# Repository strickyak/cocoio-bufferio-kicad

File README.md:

# cocoio-bufferio-kicad
for diagnostic use

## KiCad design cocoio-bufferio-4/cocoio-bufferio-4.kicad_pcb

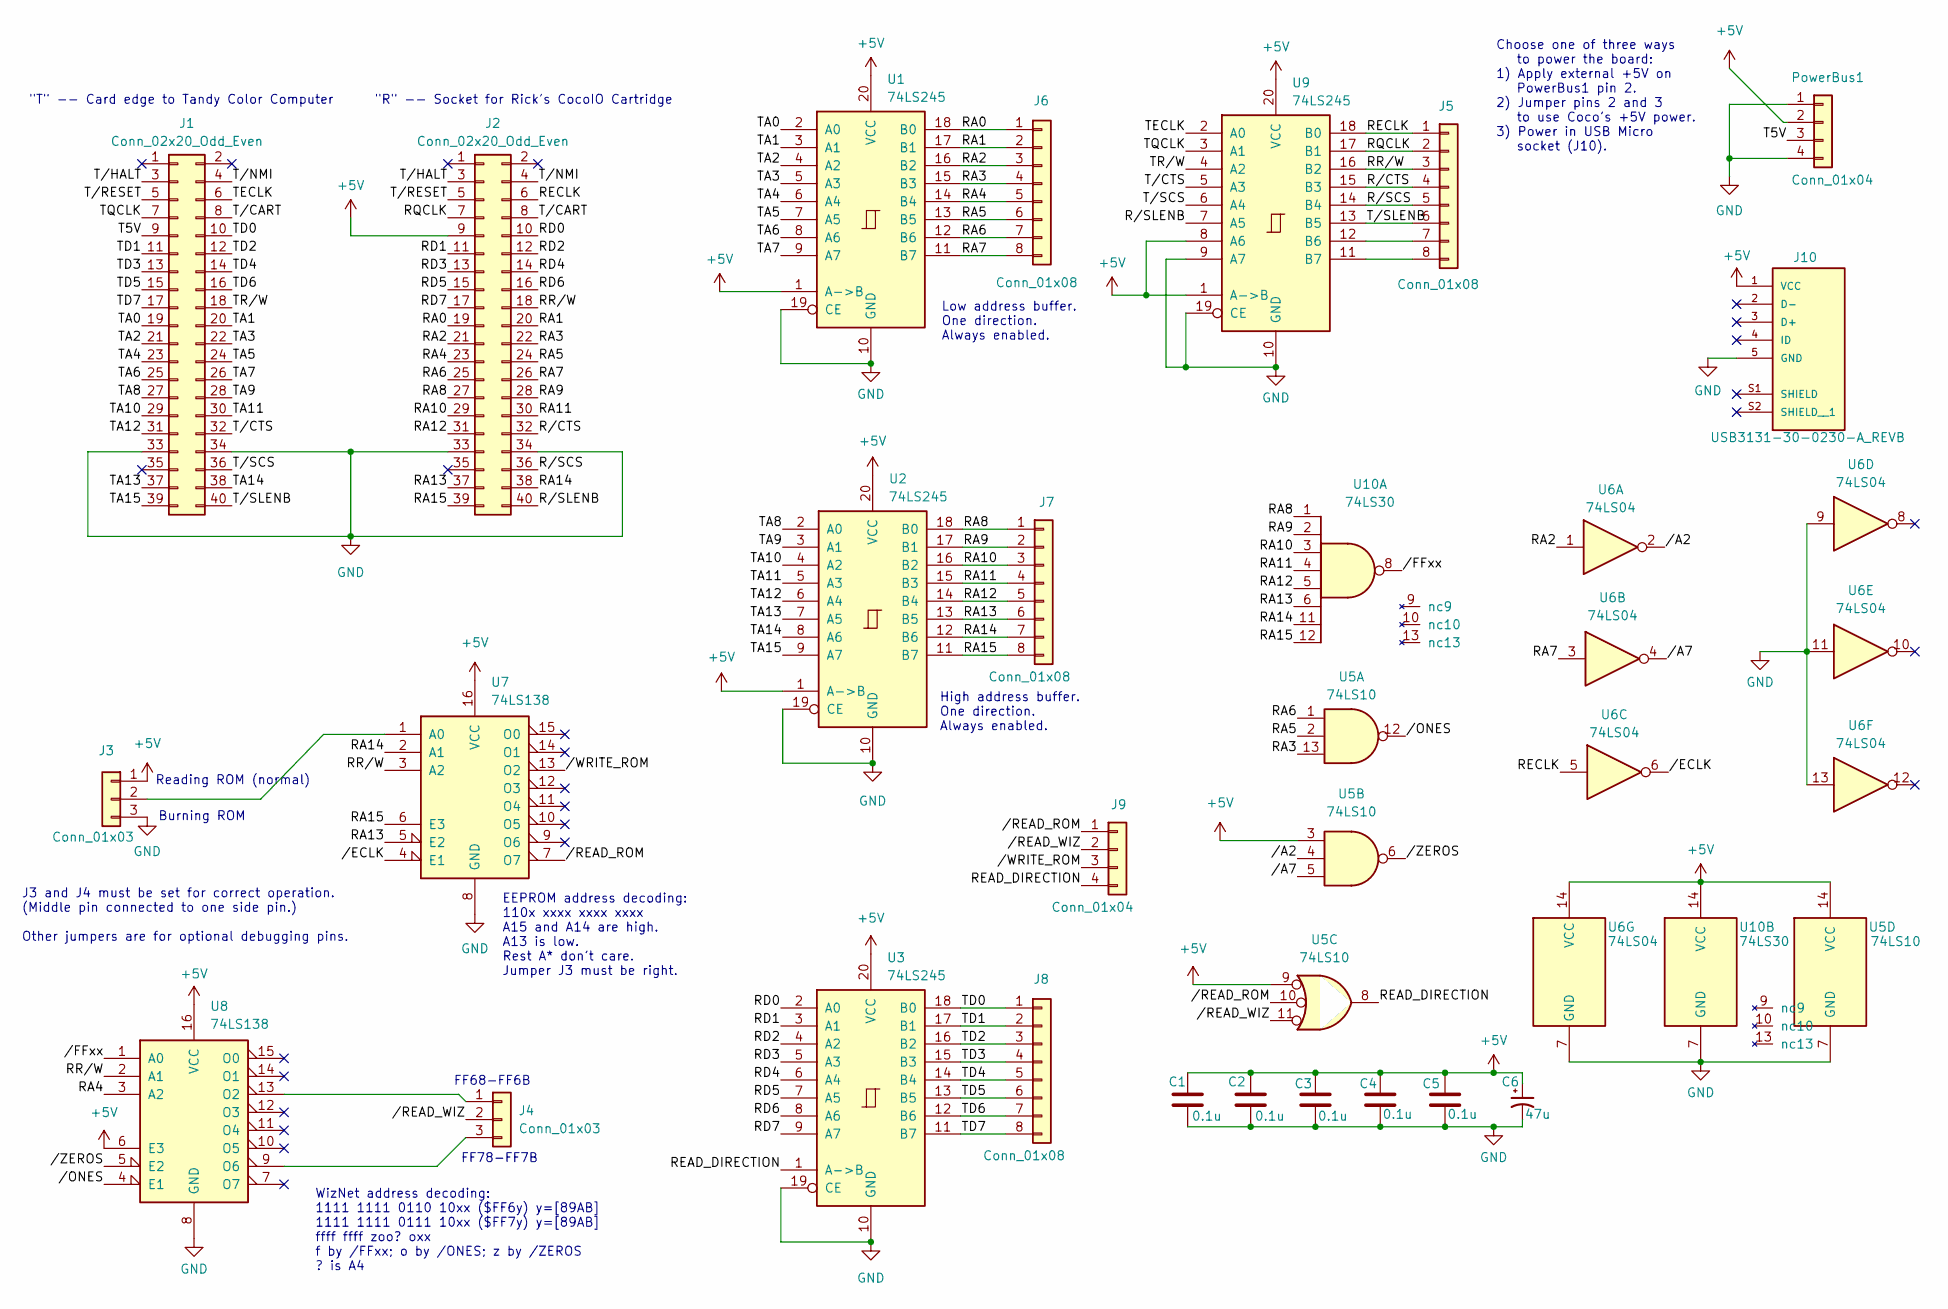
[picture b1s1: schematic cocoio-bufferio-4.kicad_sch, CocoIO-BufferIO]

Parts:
C1, C2, C3, C4, C5: 0.1u; C_Disc_D5.0mm_W2.5mm_P5.00mm
C6: 47u; CP_Radial_D7.5mm_P2.50mm
J1: Conn_02x20_Odd_Even; CocoCardEdge
J2: Conn_02x20_Odd_Even; Coco_Card_Female
J3, J4: Conn_01x03; PinHeader_1x03_P2.54mm_Vertical
J5, J6, J7, J8: Conn_01x08; PinHeader_1x08_P2.54mm_Vertical
J9: Conn_01x04; PinHeader_1x04_P2.54mm_Vertical
J10: USB3131-30-0230-A_REVB; GCT_USB3131-30-0230-A_REVB; PARTREV B4
PowerBus1: Conn_01x04; PinHeader_1x04_P2.54mm_Vertical
U1, U2, U3, U9: 74LS245; DIP-20_W7.62mm_LongPads
U5: 74LS10; DIP-14_W7.62mm_LongPads
U6: 74LS04; DIP-14_W7.62mm_LongPads
U7, U8: 74LS138; DIP-16_W7.62mm_LongPads
U10: 74LS30; DIP-14_W7.62mm_LongPads

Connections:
+5V: C1.1, C2.1, C3.1, C4.1, C5.1, C6.1, J2.9, J3.1, J10.1 (VCC), PowerBus1.2, U1.1 (A->B), U1.20 (VCC), U2.1 (A->B), U2.20 (VCC), U3.20 (VCC), U5.3, U5.9, U5.14 (VCC), U6.14 (VCC), U7.16 (VCC), U8.6 (E3), U8.16 (VCC), U9.1 (A->B), U9.8 (A6), U9.20 (VCC), U10.14 (VCC)
/RA0: J2.19, J6.1, U1.18 (B0)
/RA1: J2.20, J6.2, U1.17 (B1)
/RA2: J2.21, J6.3, U1.16 (B2), U6.1
/RA3: J2.22, J6.4, U1.15 (B3), U5.13
/RA4: J2.23, J6.5, U1.14 (B4), U8.3 (A2)
/RA5: J2.24, J6.6, U1.13 (B5), U5.2
/RA6: J2.25, J6.7, U1.12 (B6), U5.1
/RA7: J2.26, J6.8, U1.11 (B7), U6.3
/RA8: J2.27, J7.1, U2.18 (B0), U10.1
/RA9: J2.28, J7.2, U2.17 (B1), U10.2
/RA10: J2.29, J7.3, U2.16 (B2), U10.3
/RA11: J2.30, J7.4, U2.15 (B3), U10.4
/RA12: J2.31, J7.5, U2.14 (B4), U10.5
/RA13: J2.37, J7.6, U2.13 (B5), U7.5 (E2), U10.6
/RA14: J2.38, J7.7, U2.12 (B6), U7.2 (A1), U10.11
/RA15: J2.39, J7.8, U2.11 (B7), U7.6 (E3), U10.12
/RD0: J2.10, U3.2 (A0)
/RD1: J2.11, U3.3 (A1)
/RD2: J2.12, U3.4 (A2)
/RD3: J2.13, U3.5 (A3)
/RD4: J2.14, U3.6 (A4)
/RD5: J2.15, U3.7 (A5)
/RD6: J2.16, U3.8 (A6)
/RD7: J2.17, U3.9 (A7)
/READ_DIRECTION: J9.4, U3.1 (A->B), U5.8
/RECLK: J2.6, J5.1, U6.5, U9.18 (B0)
/RQCLK: J2.7, J5.2, U9.17 (B1)
/RR/W: J2.18, J5.3, U7.3 (A2), U8.2 (A1), U9.16 (B2)
/R/CTS: J2.32, J5.4, U9.15 (B3)
/R/SCS: J2.36, J5.5, U9.14 (B4)
/R/SLENB: J2.40, U9.7 (A5)
/T5V: J1.9, PowerBus1.3
/TA0: J1.19, U1.2 (A0)
/TA1: J1.20, U1.3 (A1)
/TA2: J1.21, U1.4 (A2)
/TA3: J1.22, U1.5 (A3)
/TA4: J1.23, U1.6 (A4)
/TA5: J1.24, U1.7 (A5)
/TA6: J1.25, U1.8 (A6)
/TA7: J1.26, U1.9 (A7)
/TA8: J1.27, U2.2 (A0)
/TA9: J1.28, U2.3 (A1)
/TA10: J1.29, U2.4 (A2)
/TA11: J1.30, U2.5 (A3)
/TA12: J1.31, U2.6 (A4)
/TA13: J1.37, U2.7 (A5)
/TA14: J1.38, U2.8 (A6)
/TA15: J1.39, U2.9 (A7)
/TD0: J1.10, J8.1, U3.18 (B0)
/TD1: J1.11, J8.2, U3.17 (B1)
/TD2: J1.12, J8.3, U3.16 (B2)
/TD3: J1.13, J8.4, U3.15 (B3)
/TD4: J1.14, J8.5, U3.14 (B4)
/TD5: J1.15, J8.6, U3.13 (B5)
/TD6: J1.16, J8.7, U3.12 (B6)
/TD7: J1.17, J8.8, U3.11 (B7)
/TECLK: J1.6, U9.2 (A0)
/TQCLK: J1.7, U9.3 (A1)
/TR/W: J1.18, U9.4 (A2)
/T/CART: J1.8, J2.8
/T/CTS: J1.32, U9.5 (A3)
/T/HALT: J1.3, J2.3
/T/NMI: J1.4, J2.4
/T/RESET: J1.5, J2.5
/T/SCS: J1.36, U9.6 (A4)
/T/SLENB: J1.40, J5.6, U9.13 (B5)
//A2: U5.4, U6.2
//A7: U5.5, U6.4
//ECLK: U6.6, U7.4 (E1)
//FFxx: U8.1 (A0), U10.8
//ONES: U5.12, U8.4 (E1)
//READ_ROM: J9.1, U5.10, U7.7 (O7)
//READ_WIZ: J4.2, J9.2, U5.11
//WRITE_ROM: J9.3, U7.13 (O2)
//ZEROS: U5.6, U8.5 (E2)
GND: C1.2, C2.2, C3.2, C4.2, C5.2, C6.2, J1.33, J1.34, J2.33, J2.34, J3.3, J10.5 (GND), PowerBus1.1, PowerBus1.4, U1.10 (GND), U1.19 (CE), U2.10 (GND), U2.19 (CE), U3.10 (GND), U3.19 (CE), U5.7 (GND), U6.7 (GND), U6.9, U6.11, U6.13, U7.8 (GND), U8.8 (GND), U9.9 (A7), U9.10 (GND), U9.19 (CE), U10.7 (GND); also elsewhere on the board
unnamed: J3.2, U7.1 (A0)
unnamed: J4.1, U8.13 (O2)
unnamed: J4.3, U8.9 (O6)
unnamed: J5.7, U9.12 (B6)
unnamed: J5.8, U9.11 (B7)

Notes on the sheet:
Burning ROM
WizNet address decoding: 1111 1111 0110 10xx ($FF6y) y=[89AB] 1111 1111 0111 10xx ($FF7y) y=[89AB] ffff ffff zoo? oxx f by /FFxx; o by /ONES; z by /ZEROS ? is A4
J3 and J4 must be set for correct operation. (Middle pin connected to one side pin.) Other jumpers are for optional debugging pins.
FF68-FF6B
Choose one of three ways to power the board: 1) Apply external +5V on PowerBus1 pin 2. 2) Jumper pins 2 and 3 to use Coco's +5V power. 3) Power in USB Micro socket (J10).
"R" -- Socket for Rick's CocoIO Cartridge
EEPROM address decoding: 110x xxxx xxxx xxxx A15 and A14 are high. A13 is low. Rest A* don't care. Jumper J3 must be right.
Reading ROM (normal)
FF78-FF7B
Low address buffer. One direction. Always enabled.
"T" -- Card edge to Tandy Color Computer
High address buffer. One direction. Always enabled.

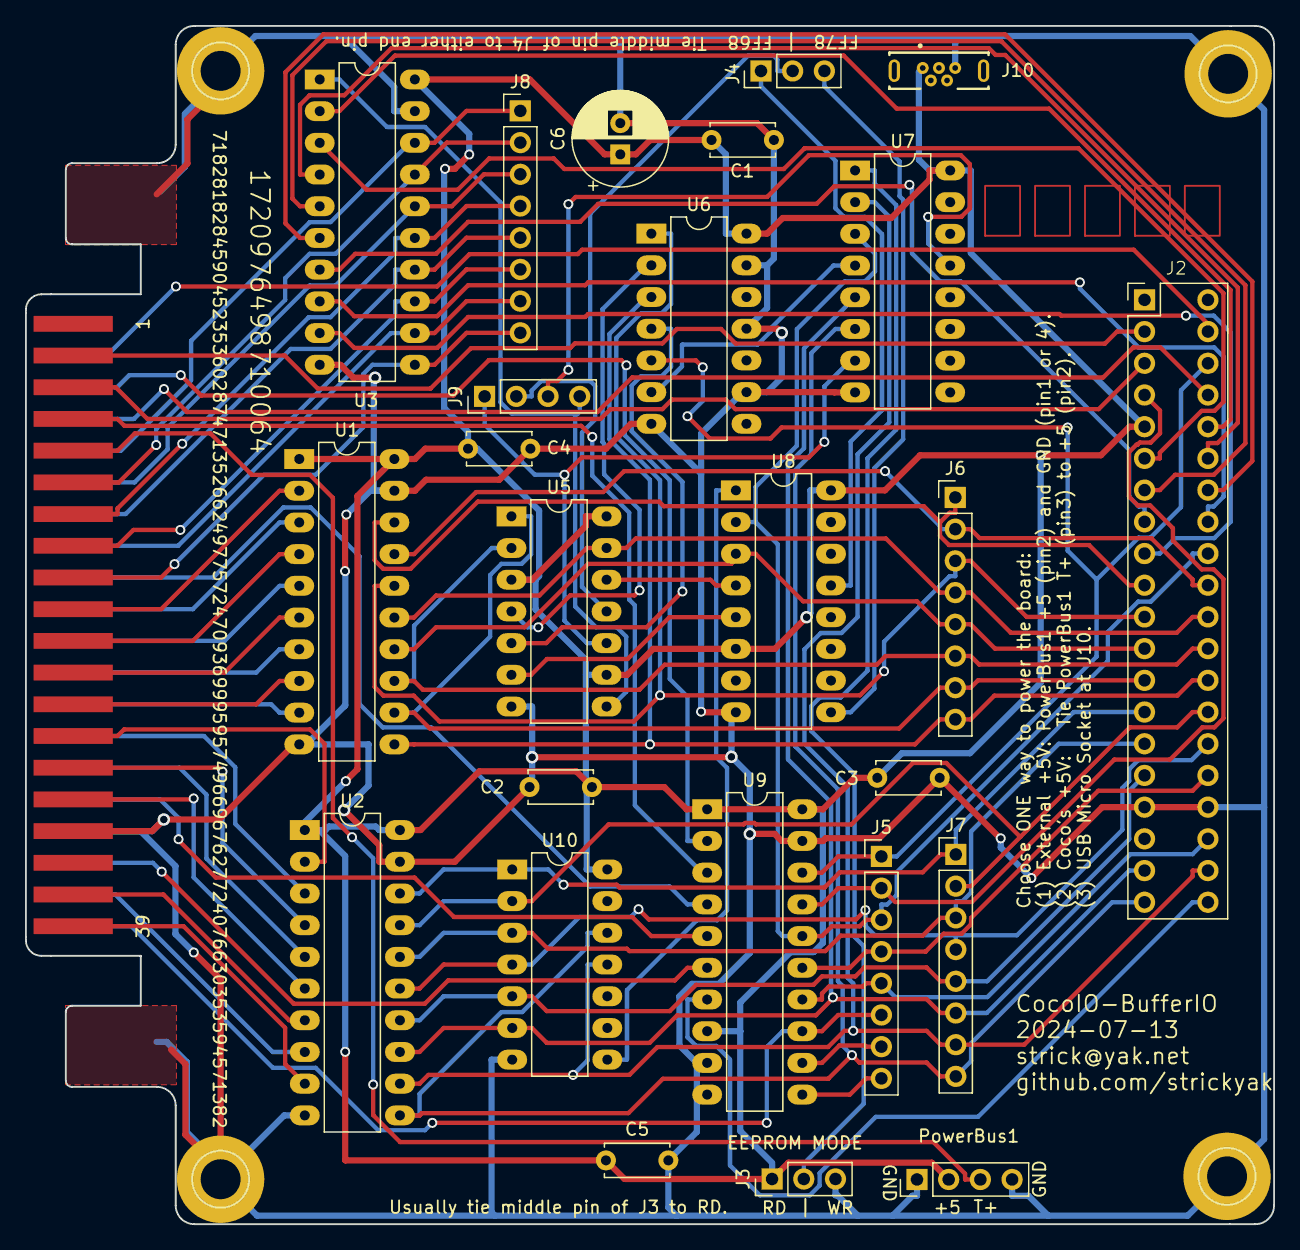
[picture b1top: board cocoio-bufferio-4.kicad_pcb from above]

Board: 2 copper layers, 100.0 x 96.0 mm, 30 parts (0 on the bottom side), 82 nets.

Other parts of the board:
GND1, GND4, GND5x, GND5y: 1pin

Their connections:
GND: GND1.1, GND4.1, GND5x.1, GND5y.1; also elsewhere on the board

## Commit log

2024-07-16 + cocoio-bufferio-4
